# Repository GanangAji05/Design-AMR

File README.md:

development of AMR robot design using Jetson Nano, ESP32, L298N driver and LiDAR sensor RPLiDAR A1.

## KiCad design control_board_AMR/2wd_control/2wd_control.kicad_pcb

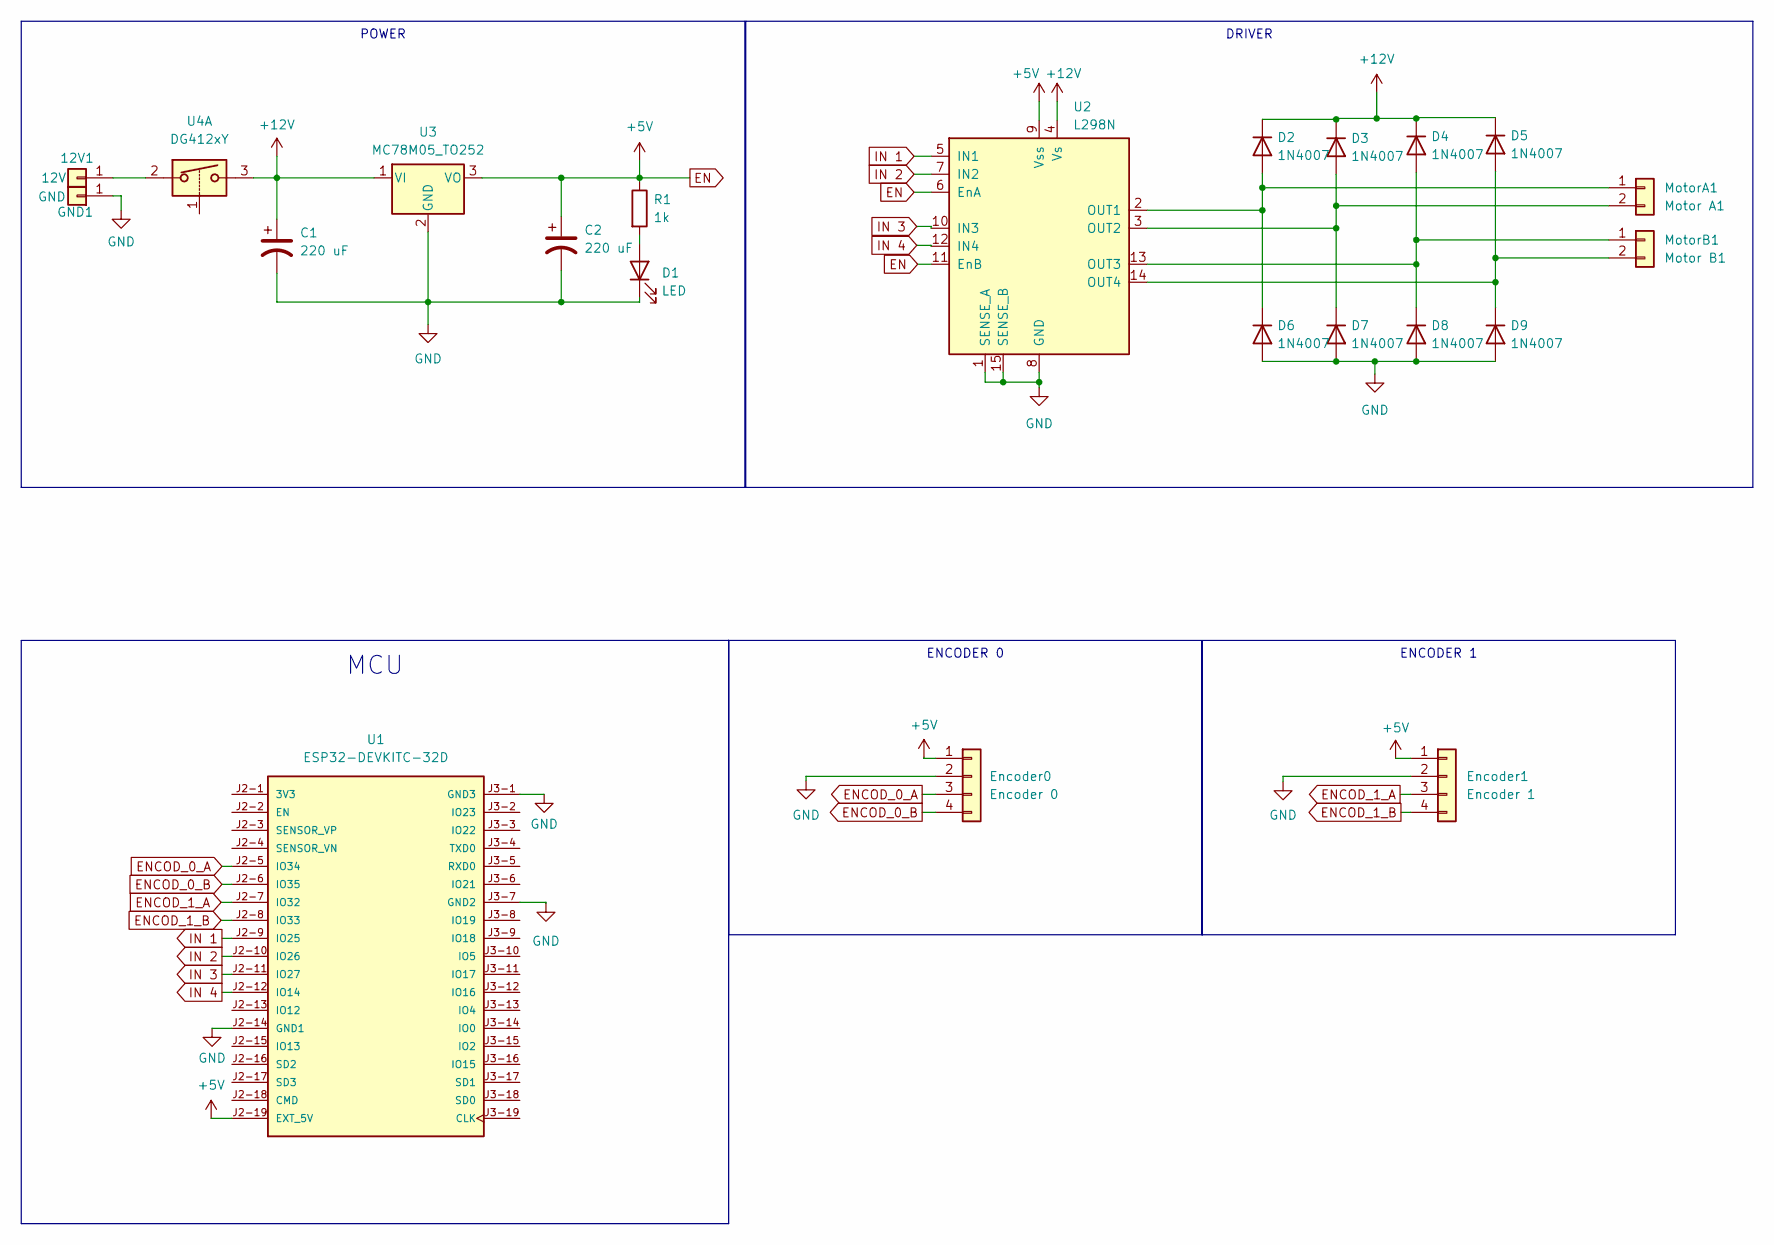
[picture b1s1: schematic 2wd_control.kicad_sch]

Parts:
12V1: 12V; Banana_Jack_1Pin
C1, C2: 220 uF; CP_Elec_10x10.5
D1: LED; LED_0805_2012Metric
D2, D3, D4, D5, D6, D7, D8, D9: 1N4007; D_SMA
Encoder0: Encoder 0; JST_XH_B4B-XH-A_1x04_P2.50mm_Vertical
Encoder1: Encoder 1; JST_XH_B4B-XH-A_1x04_P2.50mm_Vertical
GND1: GND; Banana_Jack_1Pin
MotorA1: Motor A1; JST_XH_B2B-XH-A_1x02_P2.50mm_Vertical
MotorB1: Motor B1; JST_XH_B2B-XH-A_1x02_P2.50mm_Vertical
R1: 1k; R_0805_2012Metric
U1: ESP32-DEVKITC-32D; MODULE_ESP32-DEVKITC-32D; PARTREV V4
U2: L298N; TO-220-15_P2.54x2.54mm_StaggerOdd_Lead4.58mm_Vertical
U3: MC78M05_TO252; TO-252-2
U4: DG412xY; SOIC-16_3.9x9.9mm_P1.27mm

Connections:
+12V: C1.1, D2.1 (K), D3.1 (K), D4.1 (K), D5.1 (K), U2.4 (Vs), U3.1 (VI), U4.3
EN: C2.1, Encoder0.1, Encoder1.1, R1.1, U1.J2-19 (EXT_5V), U2.6 (EnA), U2.9 (Vss), U2.11 (EnB), U3.3 (VO)
ENCOD_0_A: Encoder0.3, U1.J2-5 (IO34)
ENCOD_0_B: Encoder0.4, U1.J2-6 (IO35)
ENCOD_1_A: Encoder1.3, U1.J2-7 (IO32)
ENCOD_1_B: Encoder1.4, U1.J2-8 (IO33)
GND: C1.2, C2.2, D1.1 (K), D6.2 (A), D7.2 (A), D8.2 (A), D9.2 (A), Encoder0.2, Encoder1.2, GND1.1, U1.J2-14 (GND1), U1.J3-1 (GND3), U1.J3-7 (GND2), U2.1 (SENSE_A), U2.8 (GND), U2.15 (SENSE_B), U3.2 (GND)
IN 1: U1.J2-9 (IO25), U2.5 (IN1)
IN 2: U1.J2-10 (IO26), U2.7 (IN2)
IN 3: U1.J2-11 (IO27), U2.10 (IN3)
IN 4: U1.J2-12 (IO14), U2.12 (IN4)
unnamed: 12V1.1, U4.2
unnamed: D1.2 (A), R1.2
unnamed: D2.2 (A), D6.1 (K), MotorA1.1, U2.2 (OUT1)
unnamed: D3.2 (A), D7.1 (K), MotorA1.2, U2.3 (OUT2)
unnamed: D4.2 (A), D8.1 (K), MotorB1.1, U2.13 (OUT3)
unnamed: D5.2 (A), D9.1 (K), MotorB1.2, U2.14 (OUT4)

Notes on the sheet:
MCU
ENCODER 0
DRIVER
ENCODER 1
POWER

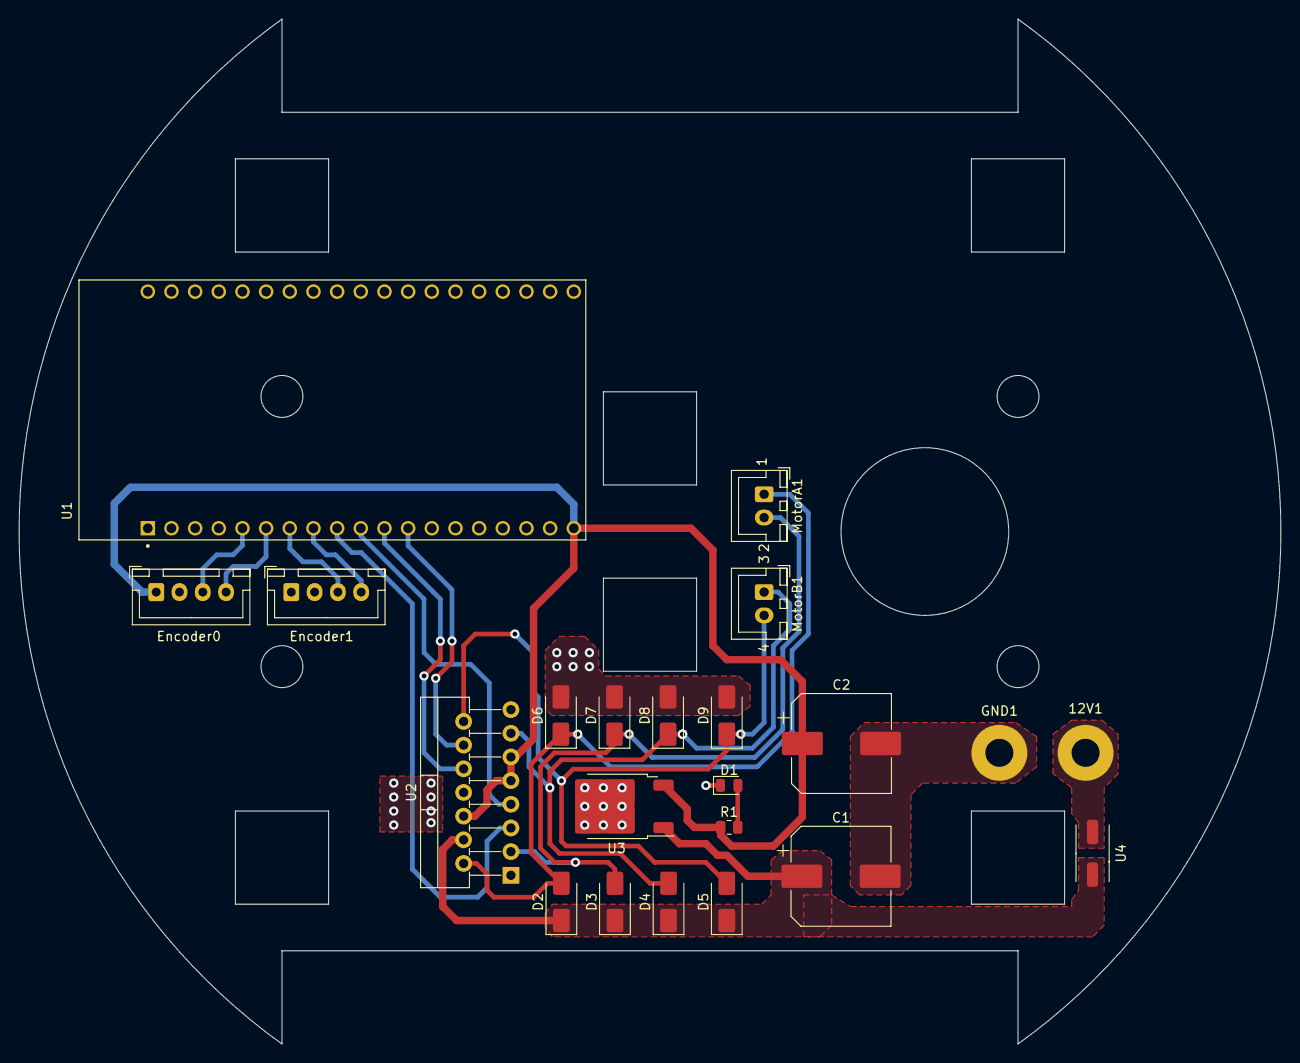
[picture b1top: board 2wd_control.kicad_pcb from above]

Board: 2 copper layers, 135.4 x 110.0 mm, 22 parts (0 on the bottom side), 17 nets.
